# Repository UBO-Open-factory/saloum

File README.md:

# saloum
Projet Saloum pour TOCIO

1.Présentation du projet
Le projet DeltaSaloum est un projet de captation de données physico-chimiques dans le delta du Saloum afin d'analyser la variabilité de l'environnement vis-à-vis de la variabilité de l'environnement.
Les données captées  sont visualisées à distance via une application Web.
Le réseau utilisé est le réseau 2G ou 3G.

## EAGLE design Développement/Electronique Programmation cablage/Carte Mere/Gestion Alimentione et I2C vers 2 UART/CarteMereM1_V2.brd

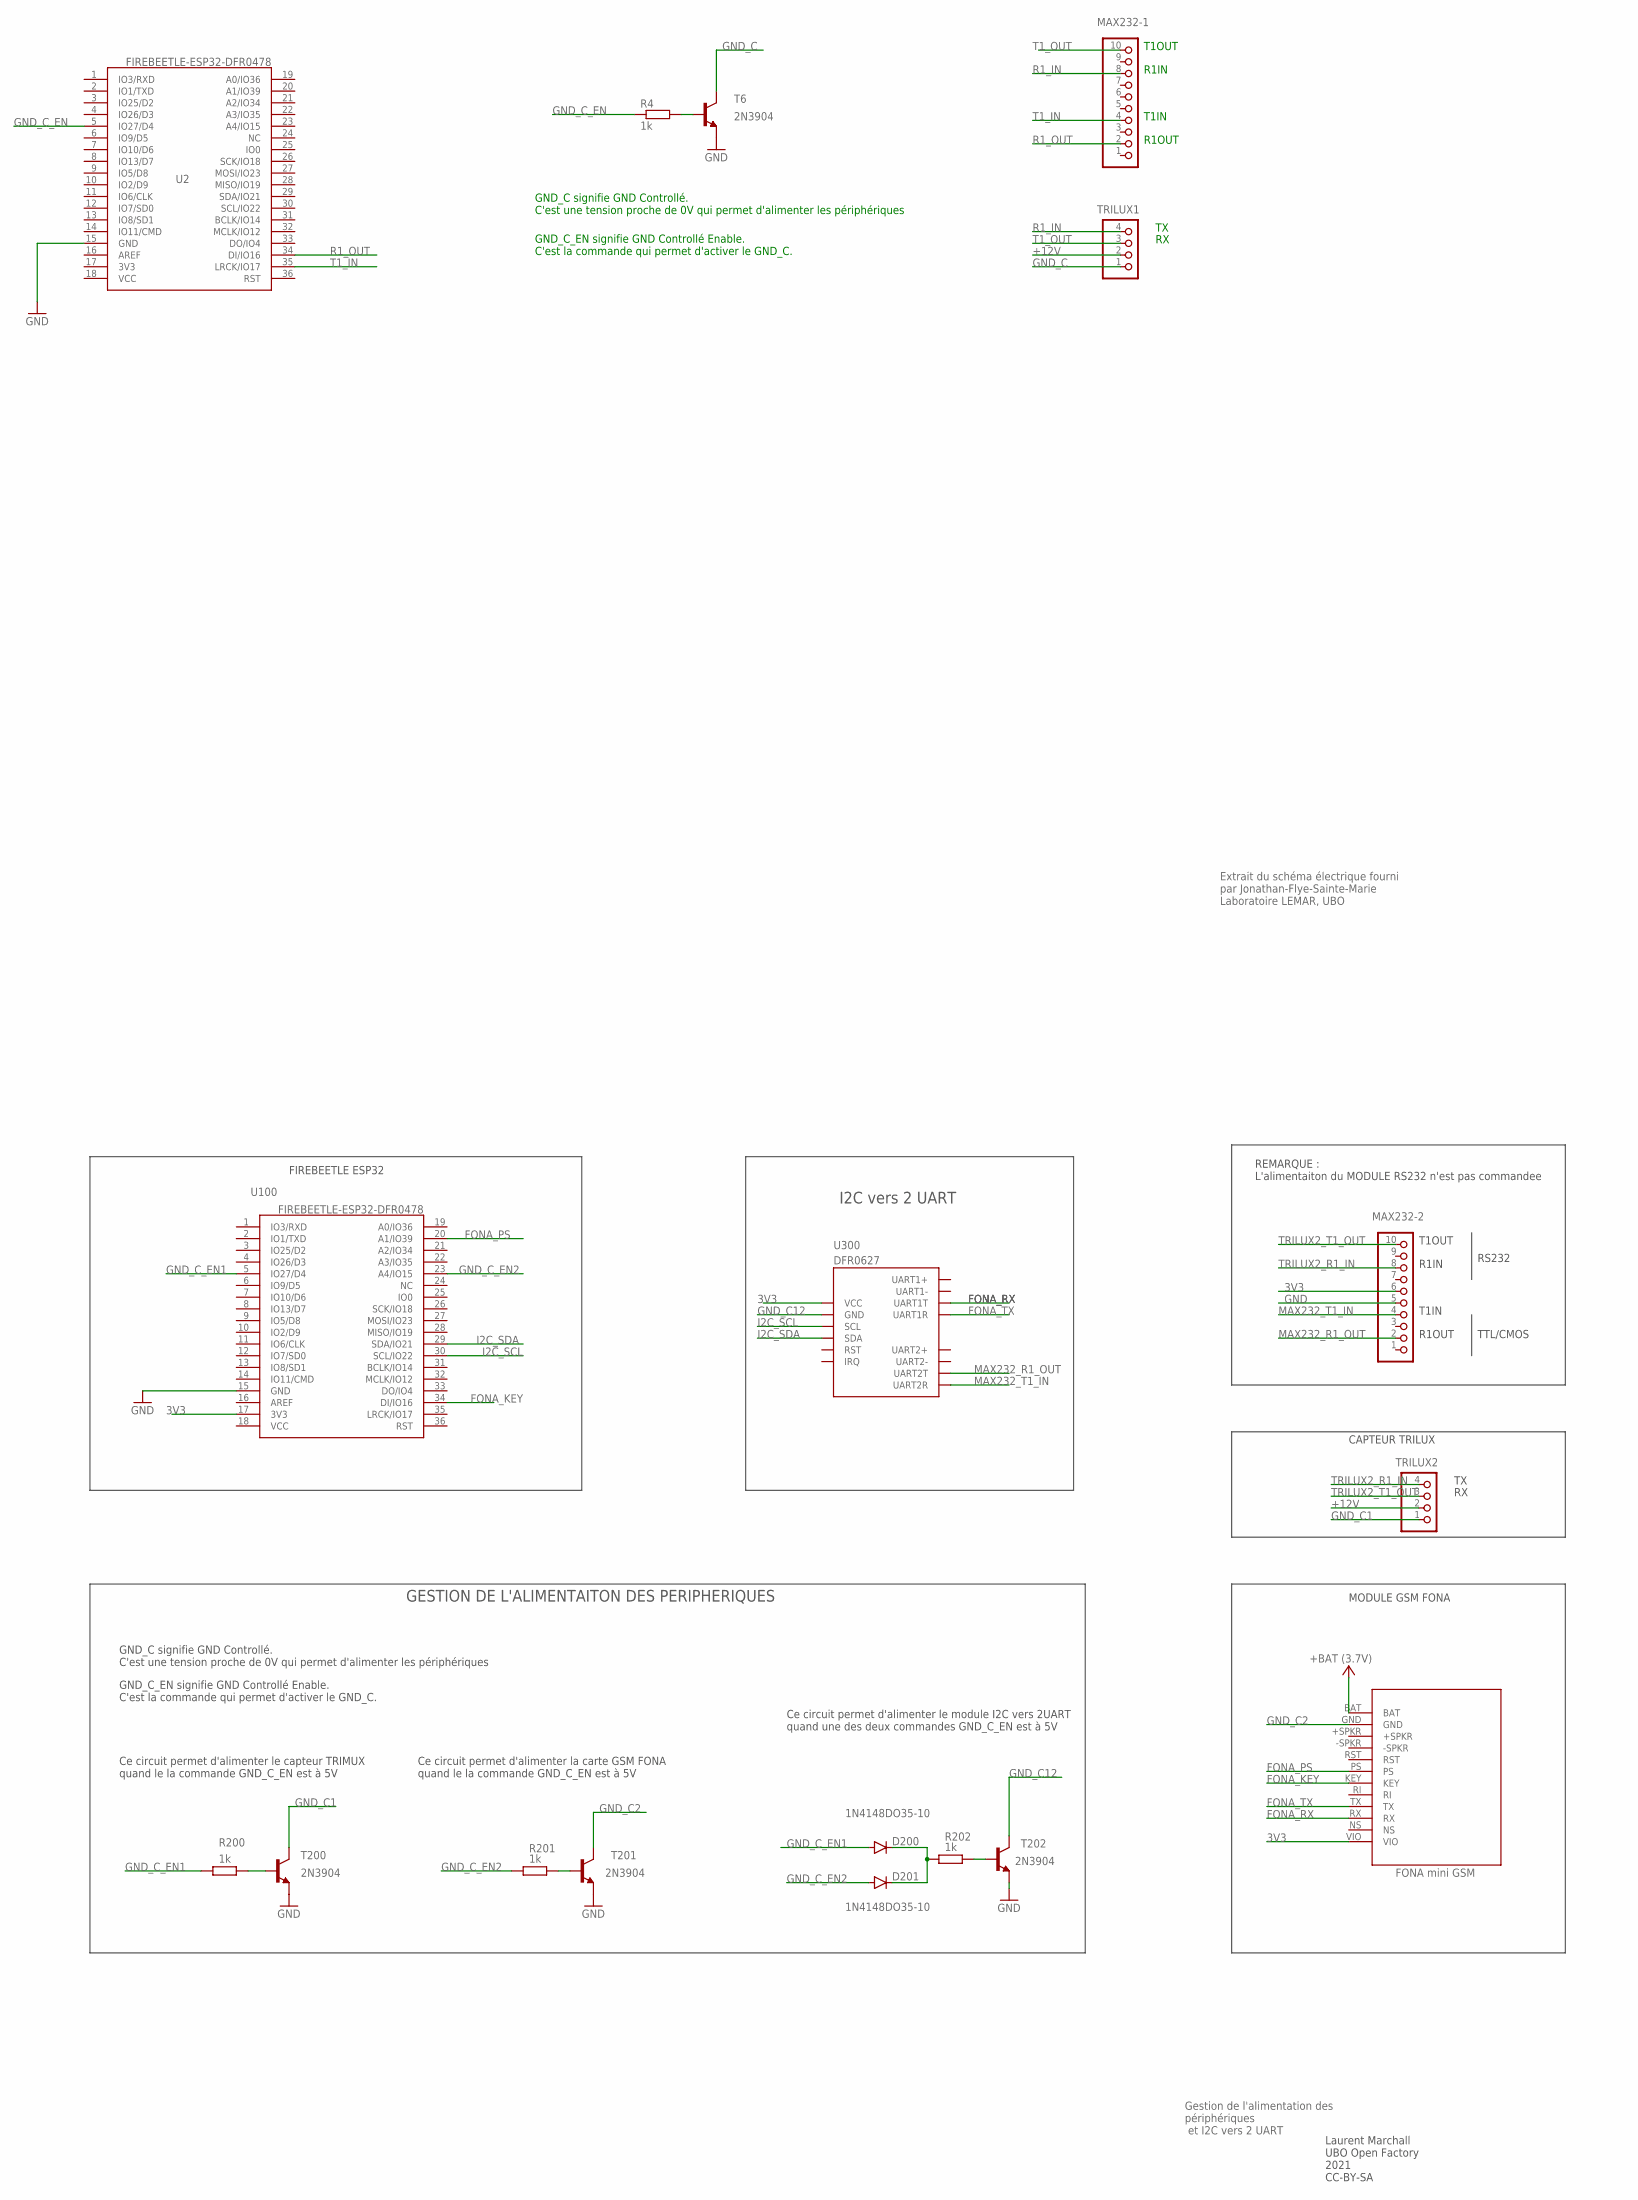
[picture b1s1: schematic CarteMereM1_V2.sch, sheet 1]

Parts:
D200, D201: 1N4148DO35-10; DO35-10
MAX232-1, MAX232-2: PINHD-1X10; 1X10
R4, R200, R201, R202: 1k; 0204/7
T6, T200, T201, T202: 2N3904; TO92
TRILUX1, TRILUX2: PINHD-1X4; 1X04
U2, U100: FIREBEETLE-ESP32-DFR0478; FIREBEETLE_ESP32
U300: DFR0627; DUAL-UART-MODULE-DFR0627
U$1: FONA_MINI_GSM

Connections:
3V3: MAX232-2.6, U100.17 (3V3), U300.VCC, U$1.VIO
+12V: TRILUX1.2, TRILUX2.2
FONA_KEY: U100.34 (DI/IO16), U$1.KEY
FONA_PS: U100.20 (A1/IO39), U$1.PS
FONA_RX: U300.UART1T, U$1.RX
FONA_TX: U300.UART1R, U$1.TX
GND: MAX232-2.5, T6.3 (E), T200.3 (E), T201.3 (E), T202.3 (E), U2.15 (GND), U100.15 (GND)
GND_C: T6.1 (C), TRILUX1.1
GND_C1: T200.1 (C), TRILUX2.1
GND_C2: T201.1 (C), U$1.GND
GND_C12: T202.1 (C), U300.GND
GND_C_EN: R4.1, U2.5 (IO27/D4)
GND_C_EN1: D200.A, R200.1, U100.5 (IO27/D4)
GND_C_EN2: D201.A, R201.1, U100.23 (A4/IO15)
I2C_SCL: U100.30 (SCL/IO22), U300.SCL
I2C_SDA: U100.29 (SDA/IO21), U300.SDA
MAX232_R1_OUT: MAX232-2.2, U300.UART2T
MAX232_T1_IN: MAX232-2.4, U300.UART2R
unnamed: R200.2, T200.2 (B)
unnamed: R201.2, T201.2 (B)
unnamed: R202.2, T202.2 (B)
unnamed: D200.C, D201.C, R202.1
unnamed: R4.2, T6.2 (B)
R1_IN: MAX232-1.8, TRILUX1.4
R1_OUT: MAX232-1.2, U2.34 (DI/IO16)
T1_IN: MAX232-1.4, U2.35 (LRCK/IO17)
T1_OUT: MAX232-1.10, TRILUX1.3
TRILUX2_R1_IN: MAX232-2.8, TRILUX2.4
TRILUX2_T1_OUT: MAX232-2.10, TRILUX2.3
VCC: U$1.BAT

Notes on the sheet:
Gestion de l'alimentation des périphériques et I2C vers 2 UART
R1OUT
T1IN
R1IN
T1OUT
GND_C signifie GND Controllé. C'est une tension proche de 0V qui permet d'alimenter les périphériques
GND_C_EN signifie GND Controllé Enable. C'est la commande qui permet d'activer le GND_C.
Ce circuit permet d'alimenter le capteur TRIMUX quand le la commande GND_C_EN est à 5V
Ce circuit permet d'alimenter la carte GSM FONA quand le la commande GND_C_EN est à 5V
Ce circuit permet d'alimenter le module I2C vers 2UART quand une des deux commandes GND_C_EN est à 5V
GESTION DE L'ALIMENTAITON DES PERIPHERIQUES
I2C vers 2 UART
Laurent Marchall UBO Open Factory 2021 CC-BY-SA
Extrait du schéma électrique fourni par Jonathan-Flye-Sainte-Marie Laboratoire LEMAR, UBO
RS232
TTL/CMOS
REMARQUE : L'alimentaiton du MODULE RS232 n'est pas commandee
MODULE GSM FONA
CAPTEUR TRILUX
FIREBEETLE ESP32

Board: 2 copper layers, 18 parts (0 on the bottom side), 29 nets, no tracks yet.

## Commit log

2021-06-15 version initiale
    Ajout de la présentation générale
2021-06-17 ajout Modif Carte mere
    - Gestion alimentaiton et module I2C vers 2UART
